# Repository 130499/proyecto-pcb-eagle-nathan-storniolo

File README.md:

# proyecto-pcb-eagle-nathan-storniolo
proyecto realizado en pcb eagle

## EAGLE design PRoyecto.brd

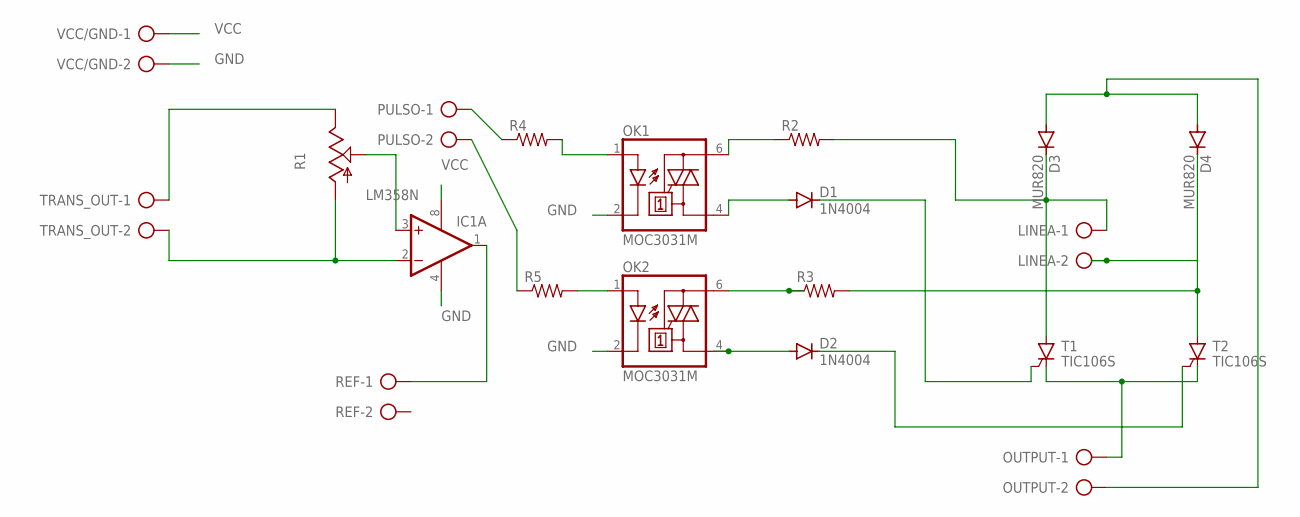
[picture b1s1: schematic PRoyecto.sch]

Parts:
D1, D2: 1N4004; DO41-10
D3, D4: MUR820; C221B1A
IC1: LM358N; DIL08
LINEA: AK500/2-H
OK1, OK2: MOC3031M; DIL06
OUTPUT: AK500/2-H
PULSO: AK500/2-H
R1: TRIM_US-CIP20C-4MM; CIP20C-4MM
R2, R3, R4, R5: R-US_0207/12; 0207/12
REF: AK500/2-H
T1, T2: TIC106S
TRANS_OUT: AK500/2-H
VCC/GND: AK500/2-H

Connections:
GND: IC1.4 (V-), OK1.2 (C), OK2.2 (C), VCC/GND.2
unnamed: OK1.1 (A), R4.2
unnamed: D4.C, LINEA.2, R3.2, T2.A
unnamed: OUTPUT.1, T1.C, T2.C
unnamed: D3.C, LINEA.1, R2.2, T1.A
unnamed: OK1.6 (A2), R2.1
unnamed: D1.A, OK1.4 (A1)
unnamed: OK2.6 (A2), R3.1
unnamed: D2.A, OK2.4 (A1)
unnamed: PULSO.1, R4.1
unnamed: D1.C, T1.G
unnamed: D2.C, T2.G
unnamed: D3.A, D4.A, OUTPUT.2
unnamed: PULSO.2, R5.1
unnamed: OK2.1 (A), R5.2
unnamed: IC1.1 (OUT), REF.1
unnamed: IC1.3 (+IN), R1.S
unnamed: IC1.2 (-IN), R1.A, TRANS_OUT.2
unnamed: R1.E, TRANS_OUT.1
VCC: IC1.8 (V+), VCC/GND.1

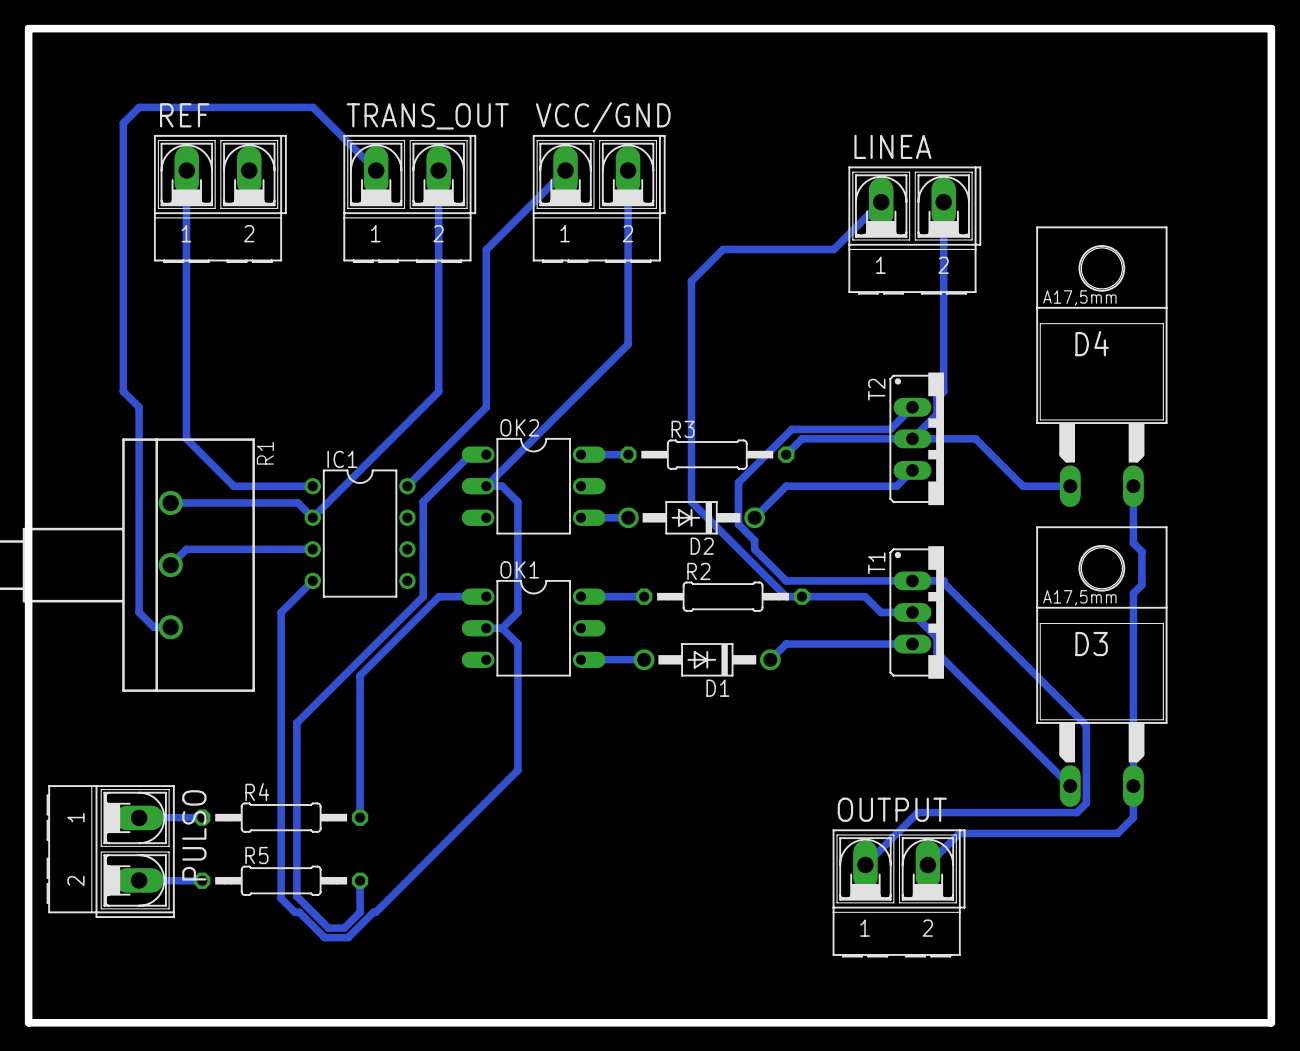
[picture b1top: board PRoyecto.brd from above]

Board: 2 copper layers, 100.0 x 80.0 mm, 20 parts (0 on the bottom side), 20 nets.
